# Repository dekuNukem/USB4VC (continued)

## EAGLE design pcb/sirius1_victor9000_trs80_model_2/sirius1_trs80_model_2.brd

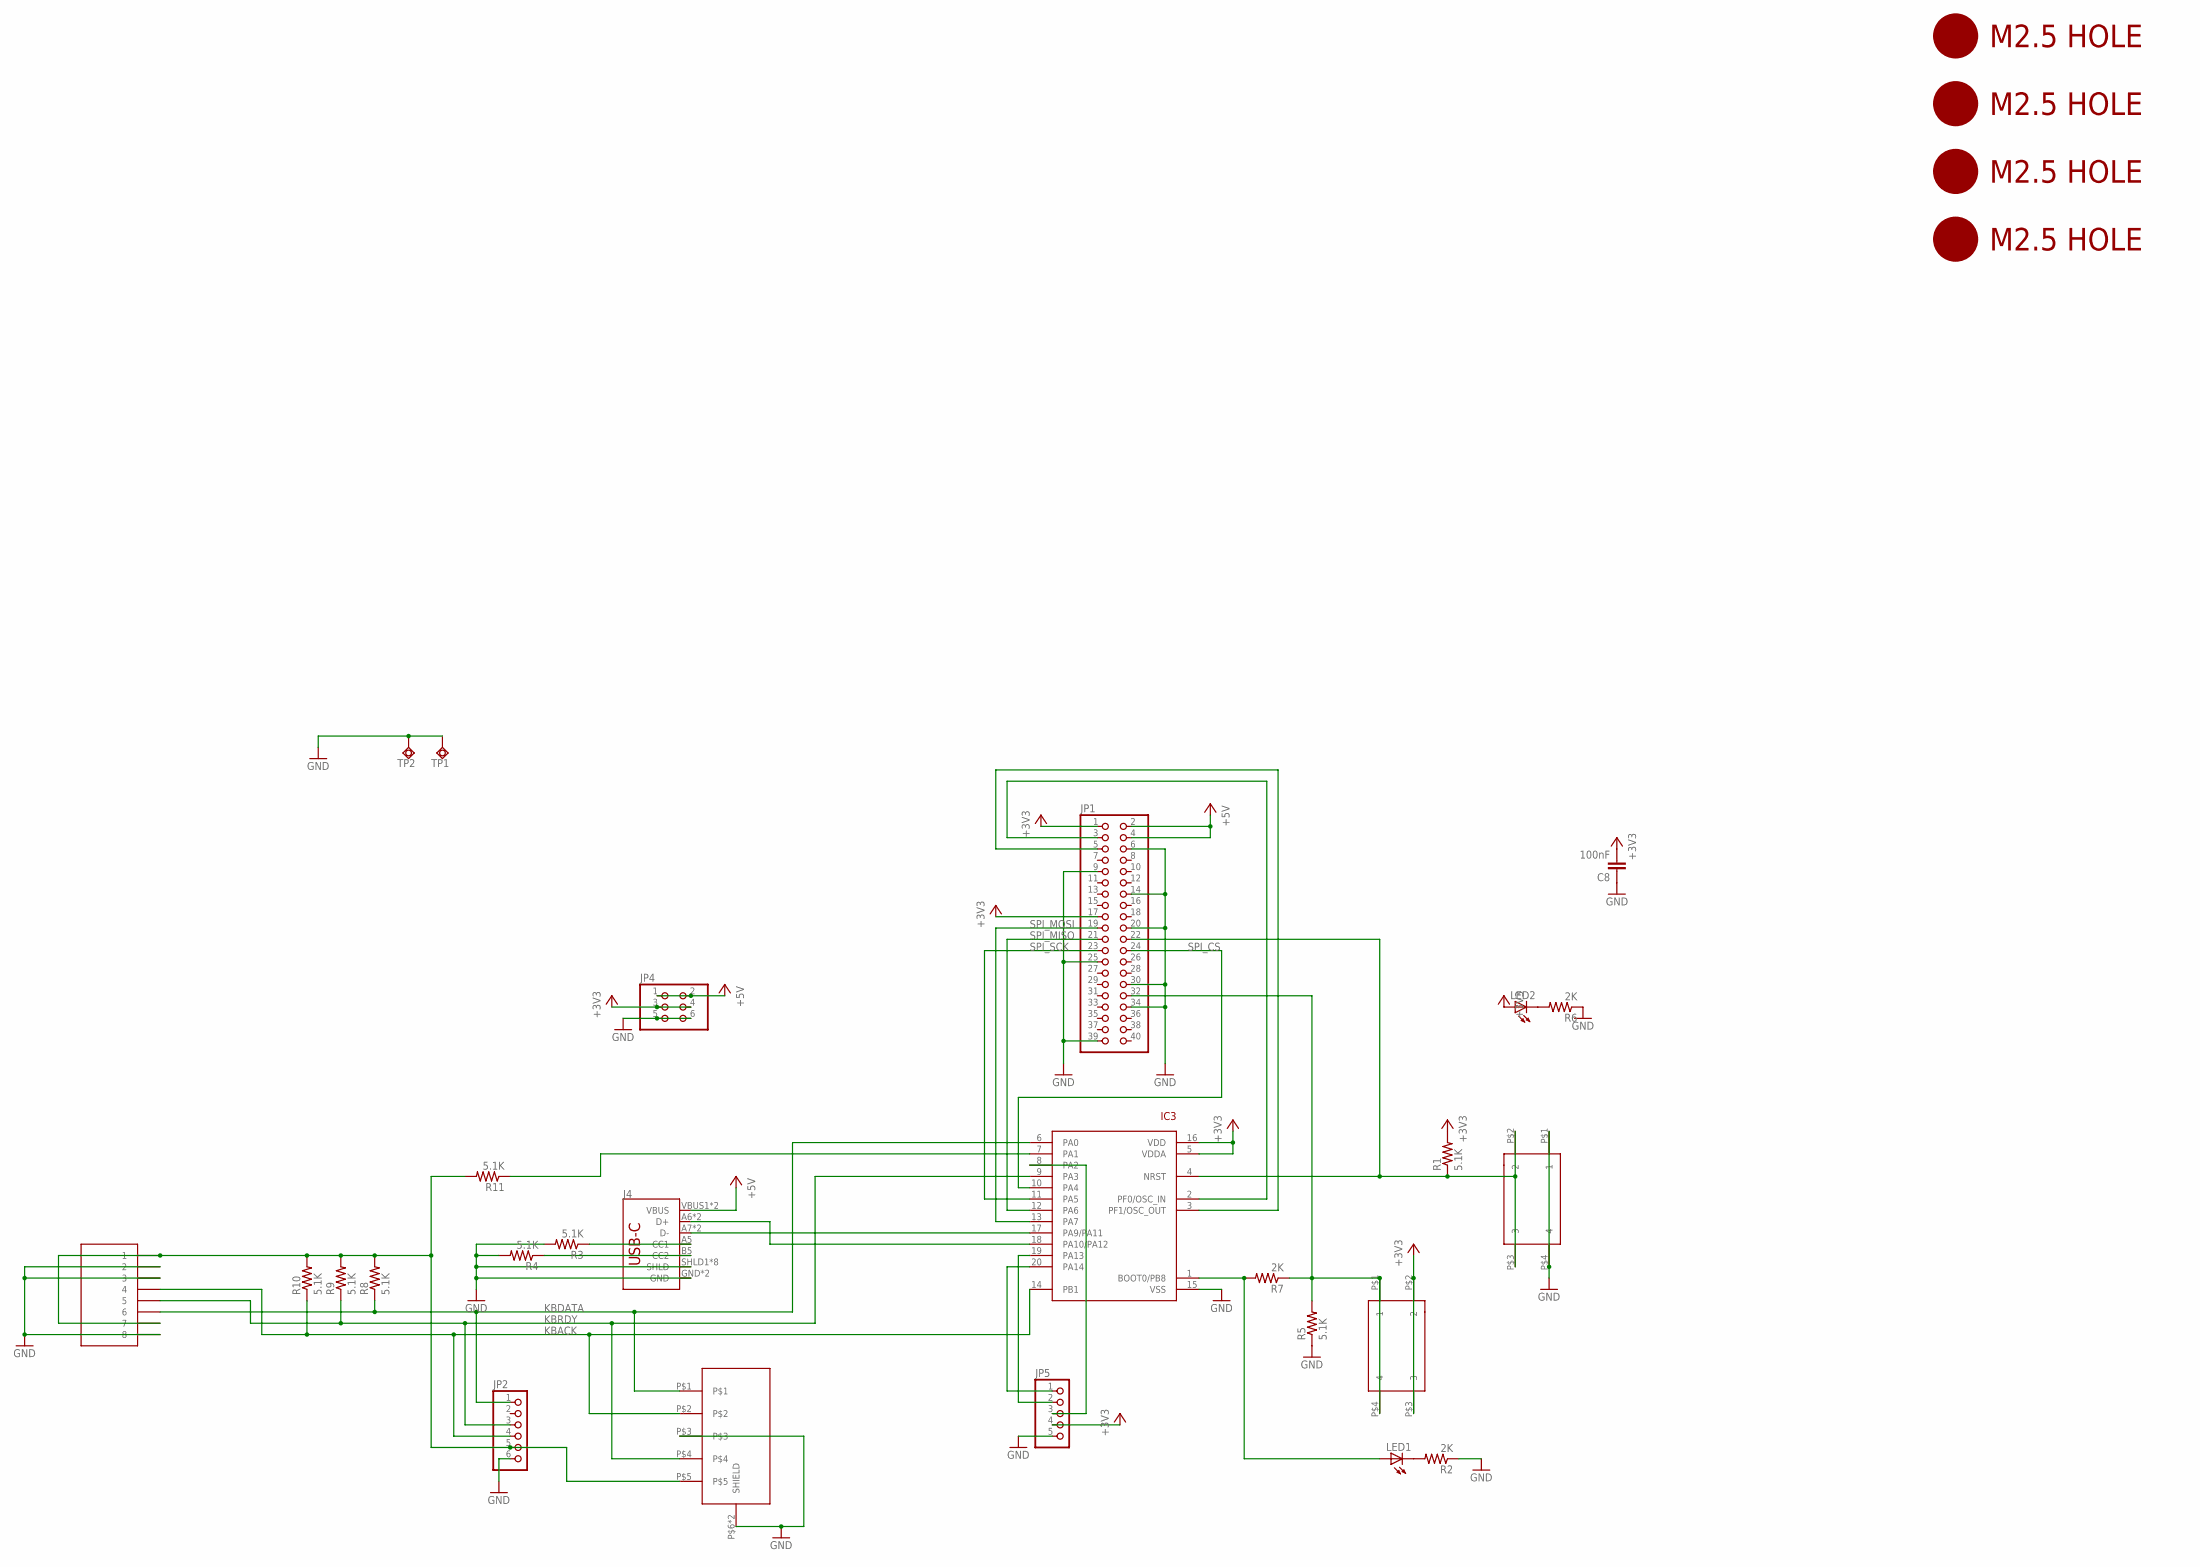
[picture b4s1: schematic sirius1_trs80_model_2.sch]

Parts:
C8: 100nF; 0805@1
IC3: STM32F042F4; TSSOP20
J4: USB_C16PIN; USB-C-16P
JP1: PINHD-2X20-BIG; 2X20-BIG
JP2: PINHD-1X6; 1X06
JP4: PINHD-2X3; 2X03
JP5: PINHD-1X5; 1X05
LED1, LED2: LEDCHIP-LED0805; CHIP-LED0805
R1, R3, R4, R5, R8, R9, R10, R11: 5.1K; 0805
R2, R6, R7: 2K; 0805
SW1, SW4: 324_SW; 342_SWICH_FOOT
TP1, TP2: TPSQPAD1-17; P1-17
U1: RJ45; RJ45-8
U$1: DIN5
U$2, U$3, U$4, U$5: M2.5HOLE

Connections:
+3V3: C8.2, IC3.5 (VDDA), IC3.16 (VDD), JP1.1, JP1.17, JP4.3, JP4.4, JP5.4, LED2.A, R1.2, SW1.P$2 (2), SW1.P$3 (3)
+5V: J4.VBUS1 (VBUS), J4.VBUS2 (VBUS), JP1.2, JP1.4, JP4.1, JP4.2
GND: C8.1, IC3.15 (VSS), J4.GND, J4.GND2 (GND), J4.SHLD1 (SHLD), J4.SHLD2 (SHLD), J4.SHLD3 (SHLD), J4.SHLD4 (SHLD), J4.SHLD5 (SHLD), J4.SHLD6 (SHLD), J4.SHLD7 (SHLD), J4.SHLD8 (SHLD), JP1.6, JP1.9, JP1.14, JP1.20, JP1.25, JP1.30, JP1.34, JP1.39, JP2.6, JP4.5, JP4.6, JP5.5, R2.1, R3.2, R4.2, R5.1, R6.1, SW4.P$1 (1), SW4.P$4 (4), TP1.TP, TP2.TP, U1.2, U1.3, U1.8, U$1.P$3, U$1.P$6 (SHIELD), U$1.P$7 (SHIELD)
KBACK: IC3.14 (PB1), JP2.4, R10.1, U1.4, U$1.P$2
KBDATA: IC3.6 (PA0), JP2.1, R8.1, U1.6, U$1.P$1
KBRDY: IC3.9 (PA3), JP2.3, R9.1, U1.5, U$1.P$4
unnamed: J4.A5 (CC1), R3.1
unnamed: JP1.32, R5.2, R7.1, SW1.P$1 (1), SW1.P$4 (4)
unnamed: IC3.17 (PA9/PA11), J4.A7 (D-), J4.B7 (D-)
unnamed: IC3.7 (PA1), R11.1
unnamed: IC3.8 (PA2), JP5.3
unnamed: IC3.19 (PA13), JP5.2
unnamed: J4.B5 (CC2), R4.1
unnamed: IC3.20 (PA14), JP5.1
unnamed: IC3.1 (BOOT0/PB8), LED1.A, R7.2
unnamed: IC3.2 (PF0/OSC_IN), JP1.3
unnamed: IC3.3 (PF1/OSC_OUT), JP1.5
unnamed: IC3.4 (NRST), JP1.22, R1.1, SW4.P$2 (2), SW4.P$3 (3)
unnamed: IC3.18 (PA10/PA12), J4.A6 (D+), J4.B6 (D+)
unnamed: LED1.C, R2.2
unnamed: JP2.5, R8.2, R9.2, R10.2, R11.2, U1.1, U1.7, U$1.P$5
unnamed: LED2.C, R6.2
SPI_CS: IC3.10 (PA4), JP1.24
SPI_MISO: IC3.12 (PA6), JP1.21
SPI_MOSI: IC3.13 (PA7), JP1.19
SPI_SCK: IC3.11 (PA5), JP1.23

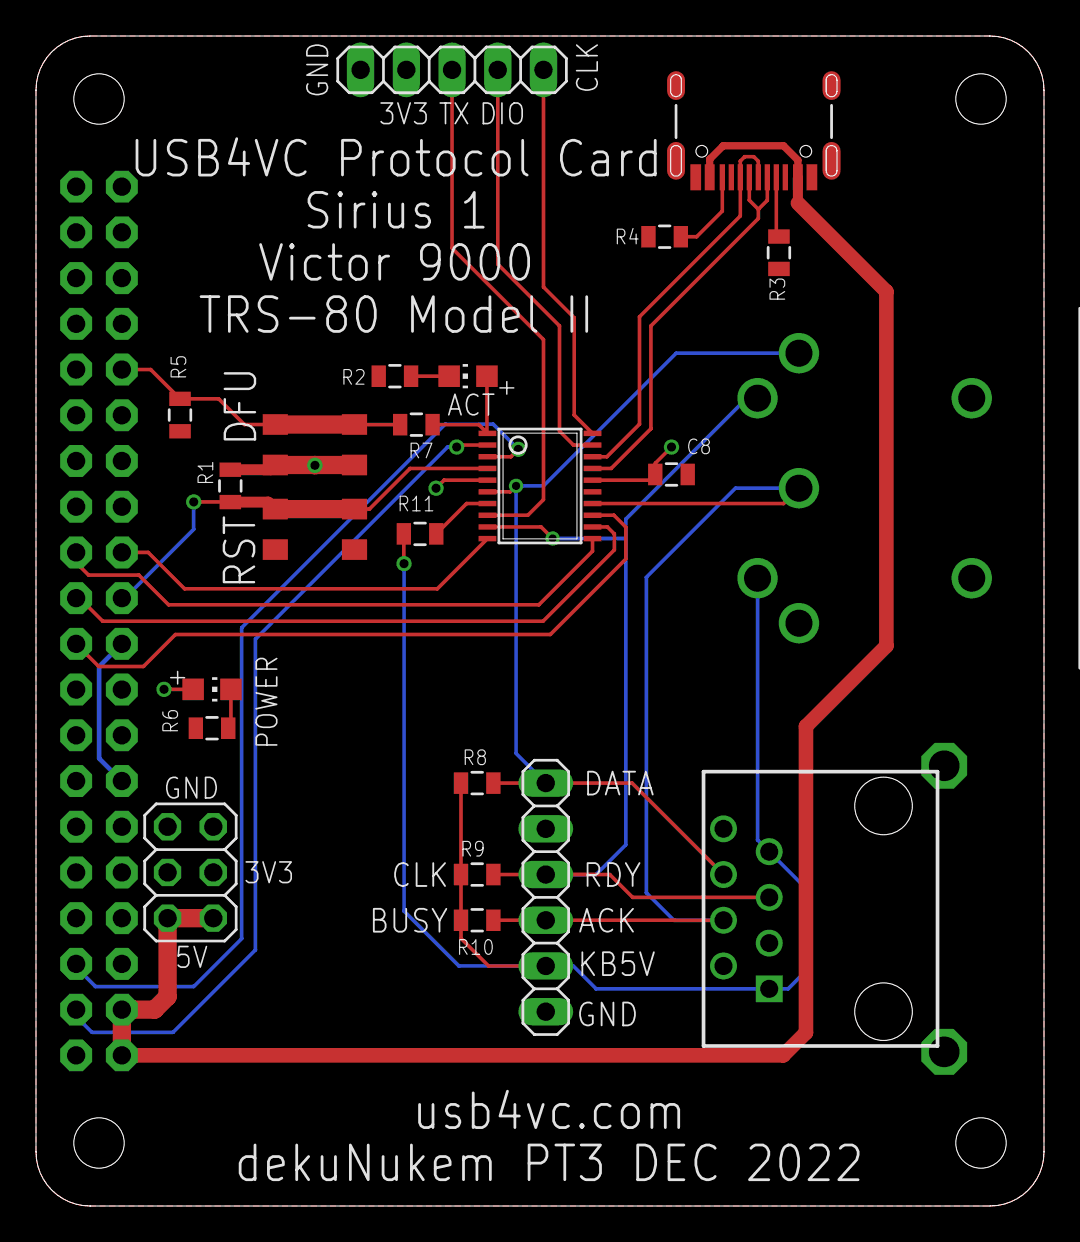
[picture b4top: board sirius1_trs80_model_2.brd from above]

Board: 2 copper layers, 56.0 x 65.0 mm, 30 parts (1 on the bottom side), 26 nets.

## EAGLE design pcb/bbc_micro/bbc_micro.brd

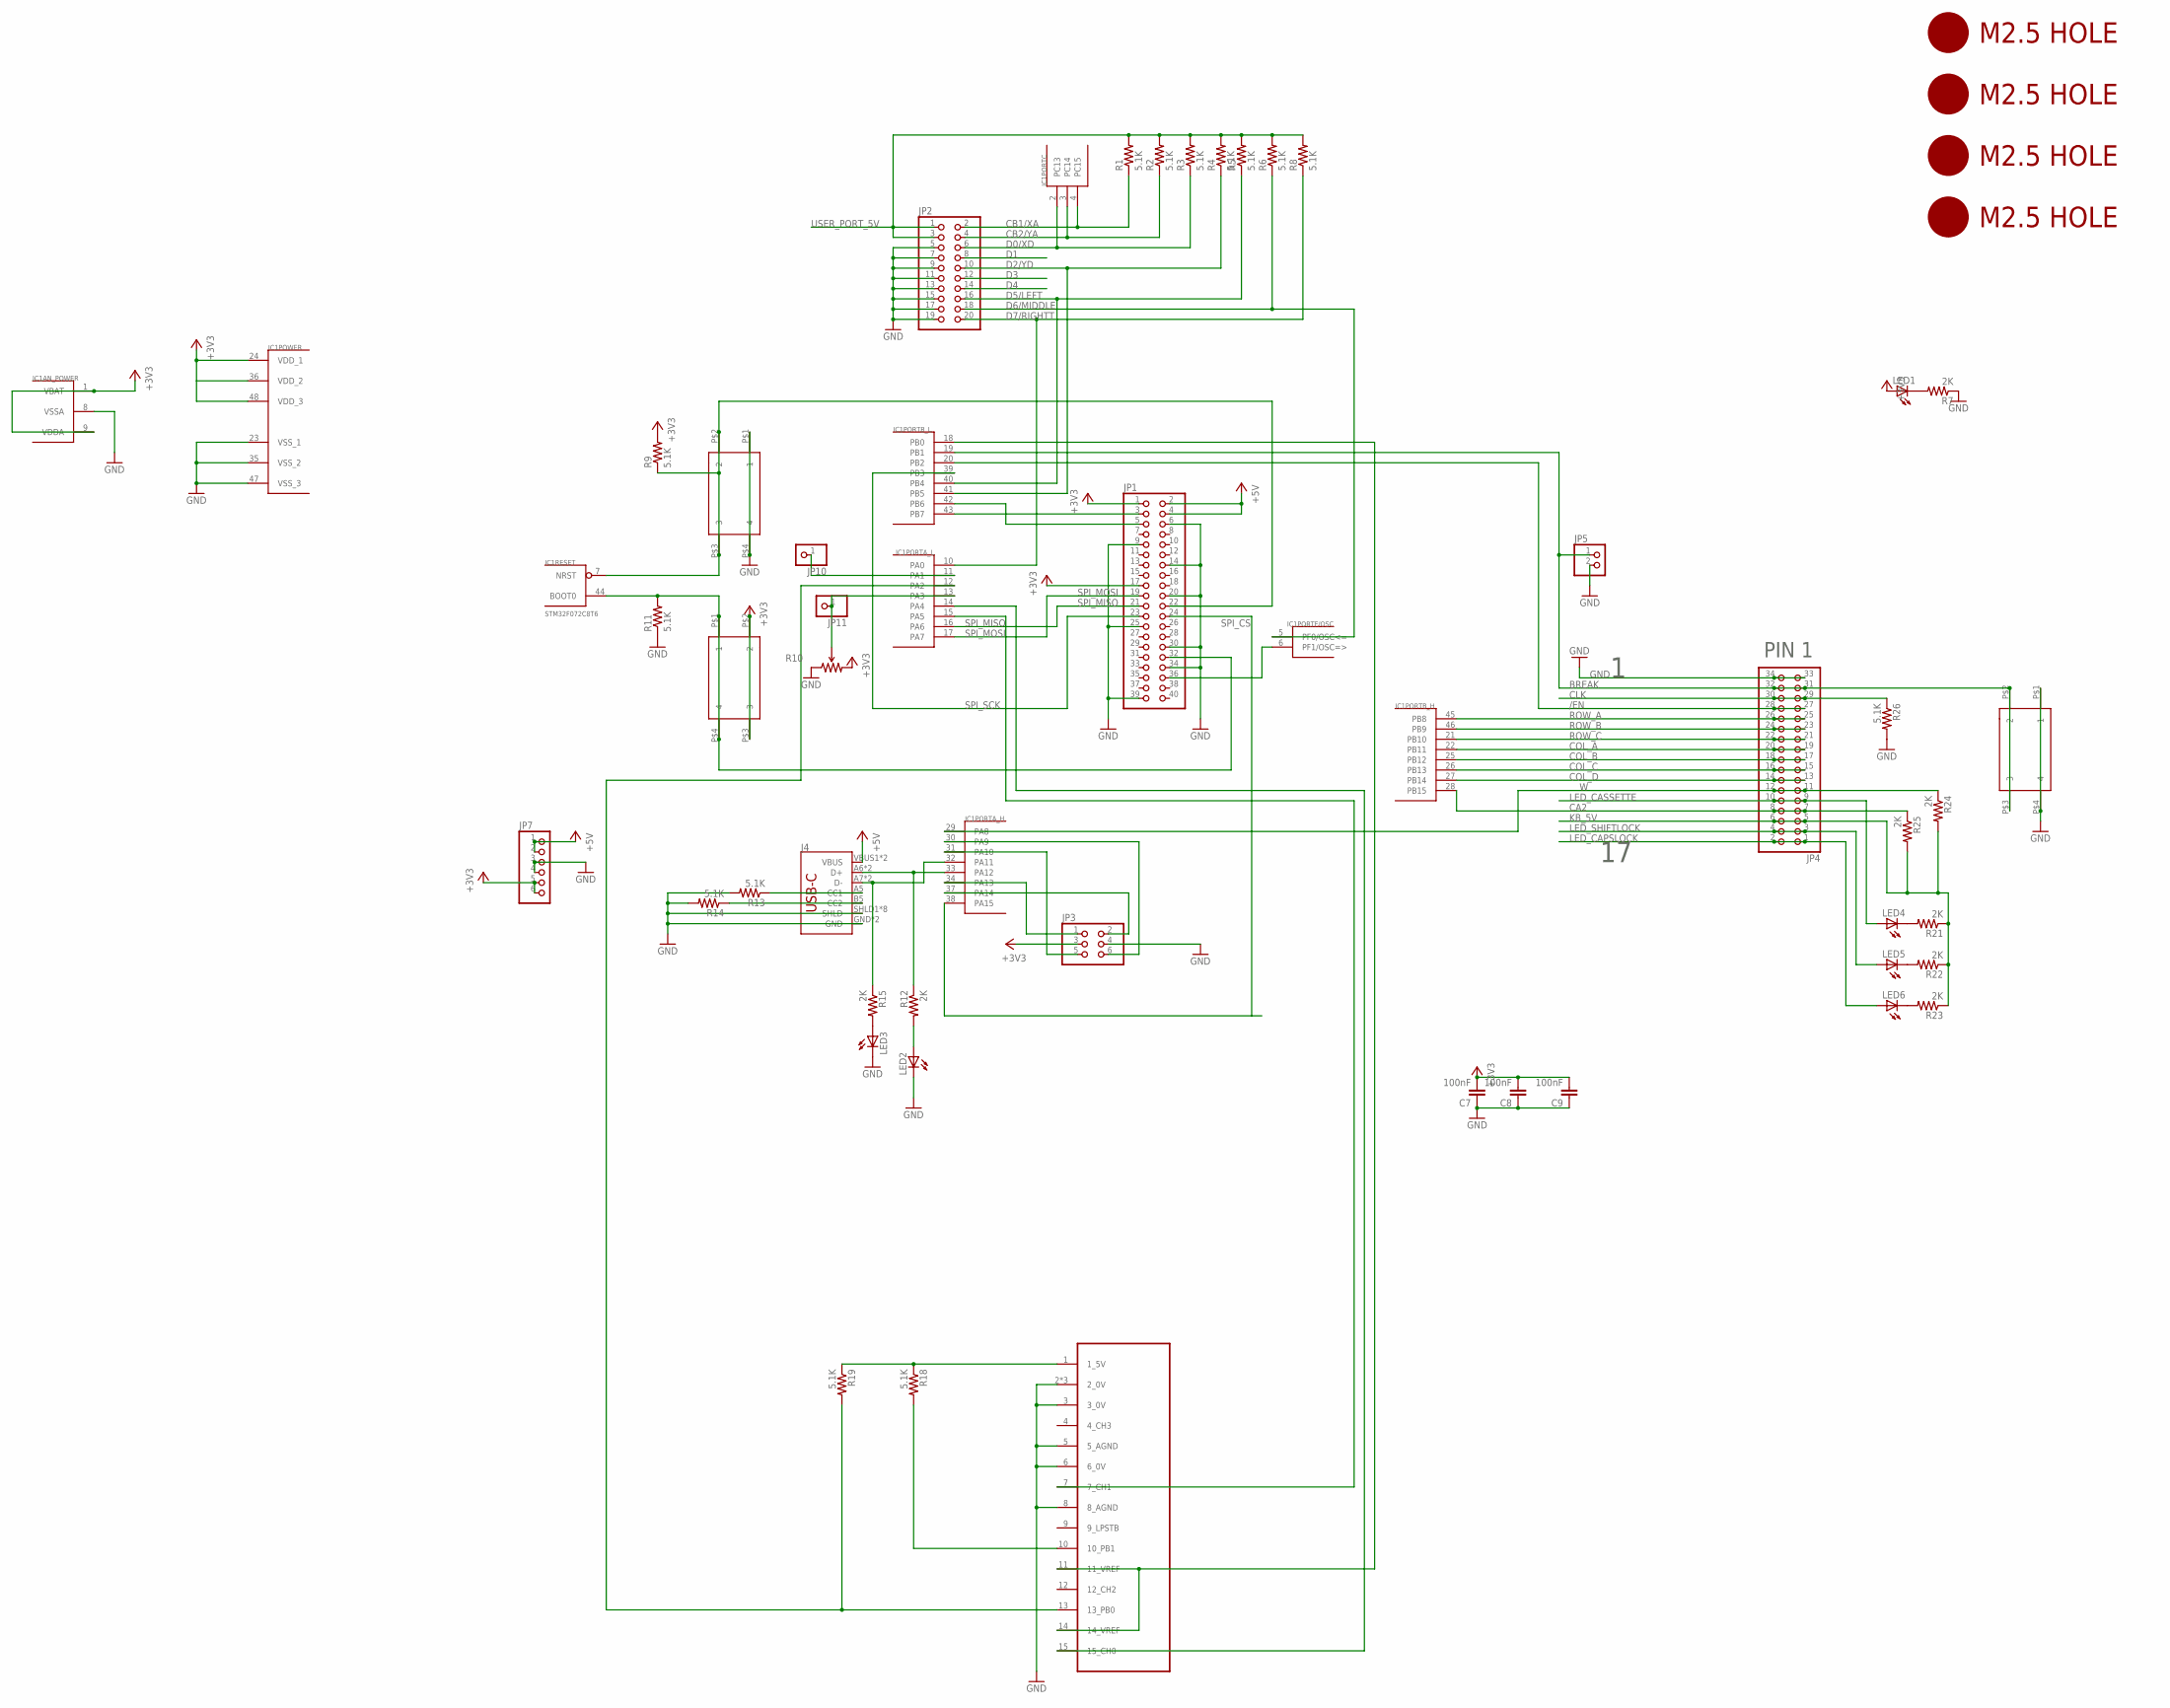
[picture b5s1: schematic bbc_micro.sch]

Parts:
C7, C8, C9: 100nF; 0805@1
IC1: STM32F072C8T6; TQFP48
J4: USB_C16PIN; USB-C-16P
JP1: PINHD-2X20-BIG; 2X20-BIG
JP2: PINHD-2X10/90; 2X10/90
JP3: PINHD-2X3; 2X03
JP4: PINHD-2X17/90; 2X17/90
JP5: PINHD-1X2; 1X02
JP7: PINHD-1X6CB; 1X06-CLEANBIG
JP10, JP11: PINHD-1X1CB; 1X01-CLEANBIG
LED1, LED2, LED3, LED4, LED5, LED6: LEDCHIP-LED0805; CHIP-LED0805
R1, R2, R3, R4, R5, R6, R8, R9, R11, R13, R14, R18, R19, R26: 5.1K; 0805
R7, R12, R15, R21, R22, R23, R24, R25: 2K; 0805
R10: TRIMPOTPTH; TRIM_POT_PTH
SW1, SW2, SW3: 324_SW; 342_SWICH_FOOT
U$2, U$3, U$6, U$7: M2.5HOLE
U$9: BBC_15P; DA15

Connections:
+3V3: C7.2, C8.2, C9.2, IC1.1 (VBAT), IC1.9 (VDDA), IC1.24 (VDD_1), IC1.36 (VDD_2), IC1.48 (VDD_3), JP1.1, JP1.17, JP3.3, JP7.5, JP7.6, LED1.A, R9.2, R10.3 (CW), SW2.P$2 (2), SW2.P$3 (3)
+5V: J4.VBUS1 (VBUS), J4.VBUS2 (VBUS), JP1.2, JP1.4, JP7.1, JP7.2
/EN: IC1.20 (PB2), JP4.27, JP4.28
BREAK: IC1.19 (PB1), JP4.31, JP4.32, JP5.1, SW3.P$2 (2), SW3.P$3 (3)
CA2: IC1.28 (PB15), JP4.7, JP4.8, R25.1
CB1/XA: IC1.4 (PC15), JP2.2, R1.1
CB2/YA: IC1.3 (PC14), JP2.4, R2.1
CLK: JP4.29, JP4.30, R26.1
COL_A: IC1.22 (PB11), JP4.19, JP4.20
COL_B: IC1.25 (PB12), JP4.17, JP4.18
COL_C: IC1.26 (PB13), JP4.15, JP4.16
COL_D: IC1.27 (PB14), JP4.13, JP4.14
D0/XD: IC1.2 (PC13), JP2.6, R3.1
D1: JP2.8
D2/YD: IC1.41 (PB5), JP2.10, R4.1
D3: JP2.12
D4: JP2.14
D5/LEFT: IC1.40 (PB4), JP2.16, R5.1
D6/MIDDLE: IC1.5 (PF0/OSC<=), JP2.18, R6.1
D7/RIGHTT: IC1.10 (PA0), JP2.20, R8.1
GND: C7.1, C8.1, C9.1, IC1.8 (VSSA), IC1.23 (VSS_1), IC1.35 (VSS_2), IC1.47 (VSS_3), J4.GND, J4.GND2 (GND), J4.SHLD1 (SHLD), J4.SHLD2 (SHLD), J4.SHLD3 (SHLD), J4.SHLD4 (SHLD), J4.SHLD5 (SHLD), J4.SHLD6 (SHLD), J4.SHLD7 (SHLD), J4.SHLD8 (SHLD), JP1.6, JP1.9, JP1.14, JP1.20, JP1.25, JP1.30, JP1.34, JP1.39, JP2.5, JP2.7, JP2.9, JP2.11, JP2.13, JP2.15, JP2.17, JP2.19, JP3.4, JP4.33, JP4.34, JP5.2, JP7.3, JP7.4, LED2.C, LED3.C, R7.1, R10.1 (CCW), R11.1, R13.2, R14.2, R26.2, SW1.P$1 (1), SW1.P$4 (4), SW3.P$1 (1), SW3.P$4 (4), U$9.2 (2_0V), U$9.3 (3_0V), U$9.5 (5_AGND), U$9.6 (6_0V), U$9.8 (8_AGND), U$9.G1 (2_0V), U$9.G2 (2_0V)
KB_5V: JP4.5, JP4.6, R21.1, R22.1, R23.1, R24.2, R25.2
LED_CAPSLOCK: JP4.1, JP4.2, LED6.A
LED_CASSETTE: JP4.9, JP4.10, LED4.A
LED_SHIFTLOCK: JP4.3, JP4.4, LED5.A
unnamed: J4.A5 (CC1), R13.1
unnamed: LED2.A, R12.2
unnamed: LED4.C, R21.2
unnamed: IC1.14 (PA4), U$9.15 (15_CH0)
unnamed: IC1.15 (PA5), U$9.7 (7_CH1)
unnamed: IC1.31 (PA10), JP3.5
unnamed: J4.B5 (CC2), R14.1
unnamed: IC1.33 (PA12), J4.A6 (D+), J4.B6 (D+), R12.1
unnamed: IC1.32 (PA11), J4.A7 (D-), J4.B7 (D-), R15.1
unnamed: IC1.18 (PB0), U$9.11 (11_VREF), U$9.14 (14_VREF)
unnamed: IC1.11 (PA1), JP10.1
unnamed: IC1.13 (PA3), JP11.1, R10.2 (WIPER)
unnamed: IC1.7 (NRST), JP1.22, R9.1, SW1.P$2 (2), SW1.P$3 (3)
unnamed: IC1.30 (PA9), JP3.6
unnamed: IC1.34 (PA13), JP3.1
unnamed: IC1.37 (PA14), JP3.2
unnamed: IC1.44 (BOOT0), JP1.32, R11.2, SW2.P$1 (1), SW2.P$4 (4)
unnamed: R18.1, R19.1, U$9.1 (1_5V)
unnamed: R18.2, U$9.10 (10_PB1)
unnamed: IC1.42 (PB6), JP1.5
unnamed: IC1.43 (PB7), JP1.3
unnamed: LED5.C, R22.2
unnamed: LED6.C, R23.2
unnamed: LED3.A, R15.2
unnamed: LED1.C, R7.2
unnamed: IC1.12 (PA2), R19.2, U$9.13 (13_PB0)
unnamed: IC1.6 (PF1/OSC=>), JP1.36
ROW_A: IC1.45 (PB8), JP4.25, JP4.26
ROW_B: IC1.46 (PB9), JP4.23, JP4.24
ROW_C: IC1.21 (PB10), JP4.21, JP4.22
SPI_CS: IC1.38 (PA15), JP1.24
SPI_MISO: IC1.16 (PA6), JP1.21
SPI_MOSI: IC1.17 (PA7), JP1.19
SPI_SCK: IC1.39 (PB3), JP1.23
USER_PORT_5V: JP2.1, JP2.3, R1.2, R2.2, R3.2, R4.2, R5.2, R6.2, R8.2
W: IC1.29 (PA8), JP4.11, JP4.12, R24.1

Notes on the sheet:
PIN 1

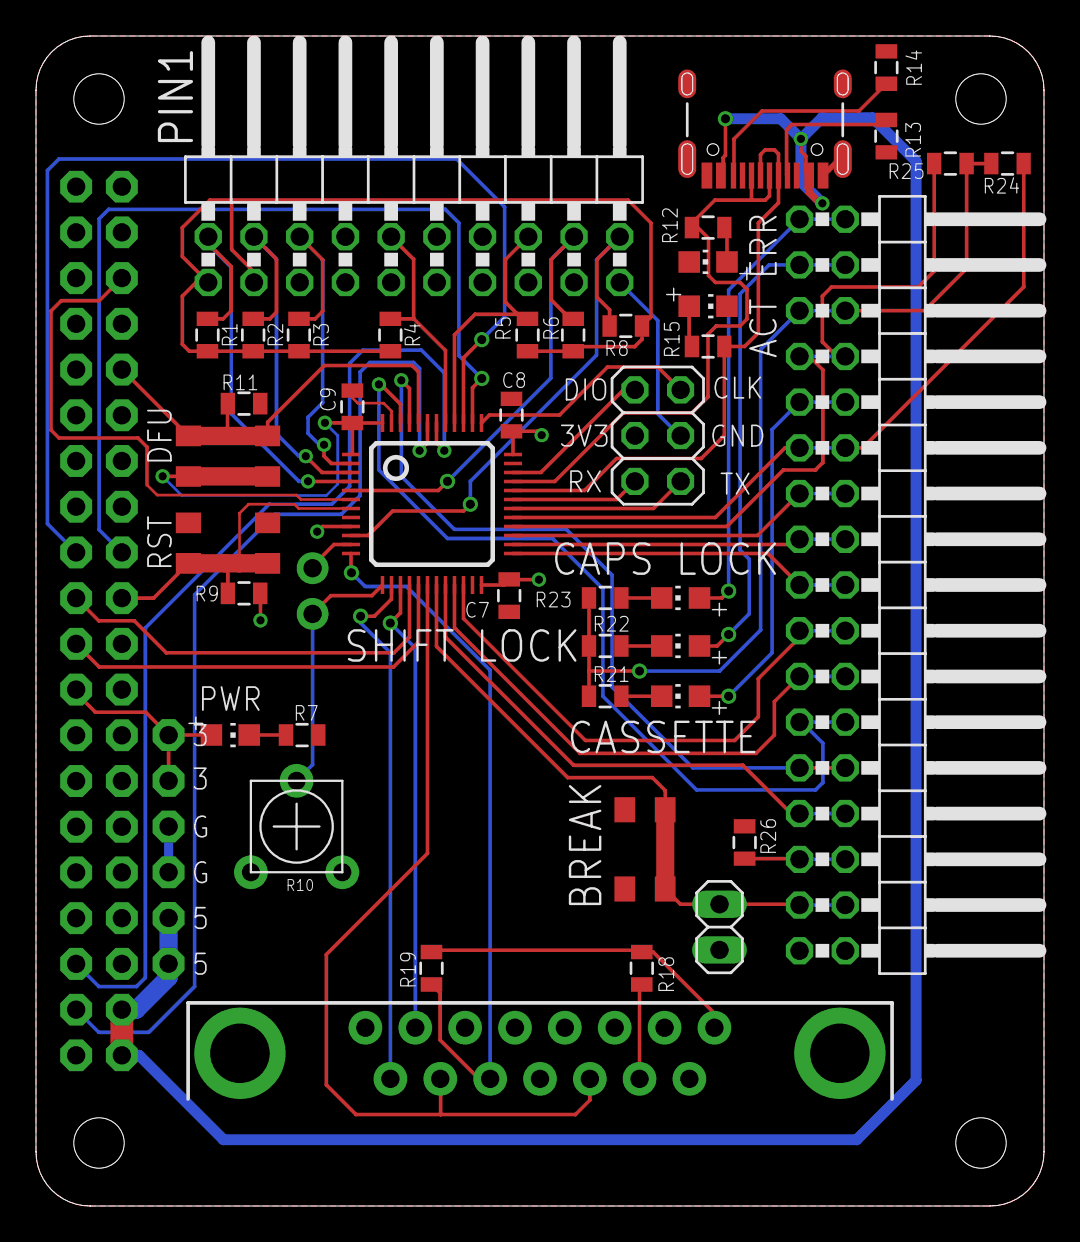
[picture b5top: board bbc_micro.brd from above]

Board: 2 copper layers, 56.0 x 65.0 mm, 50 parts (1 on the bottom side), 58 nets.

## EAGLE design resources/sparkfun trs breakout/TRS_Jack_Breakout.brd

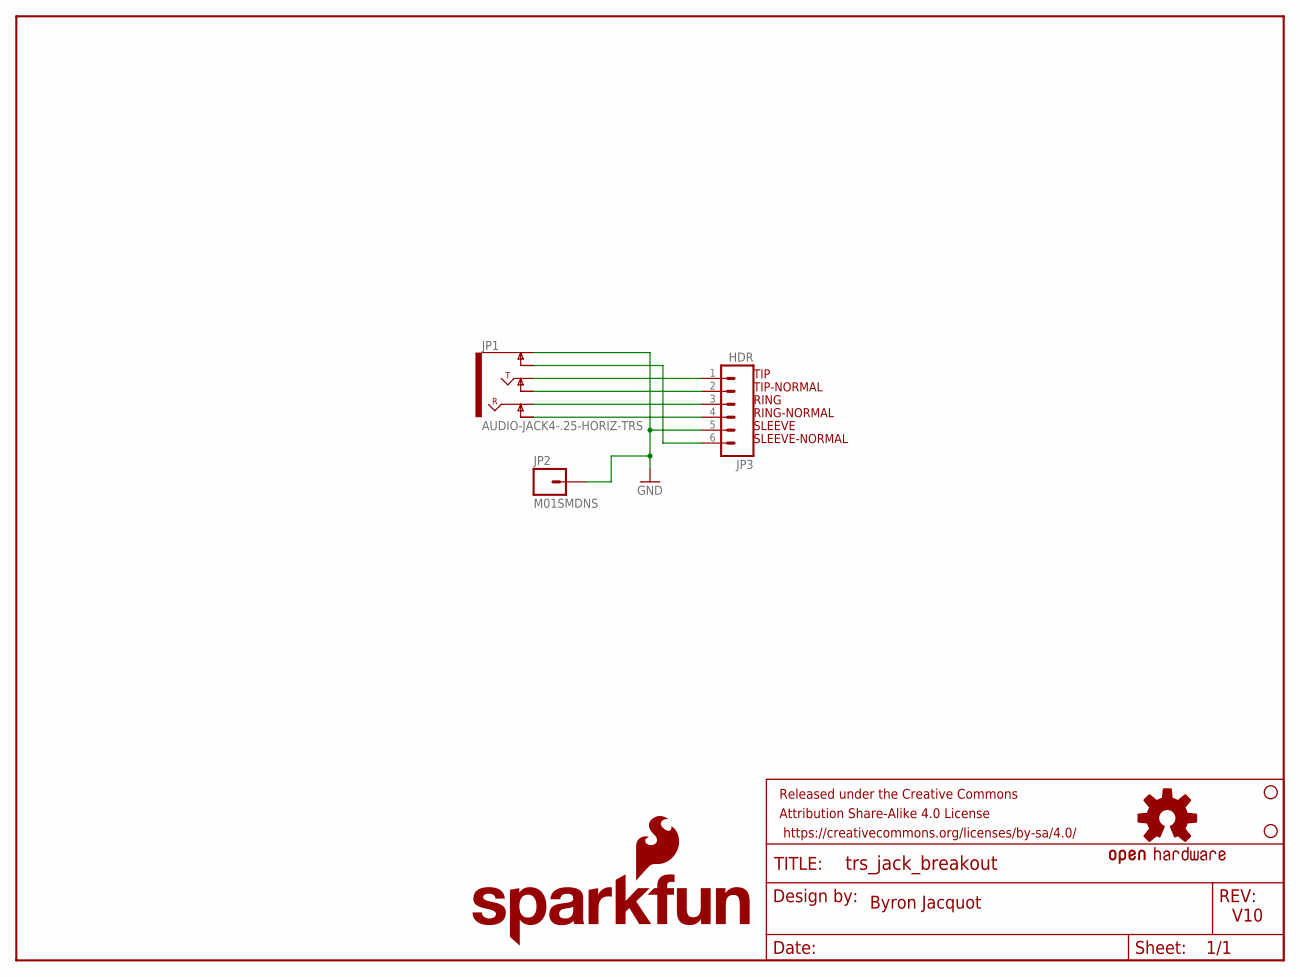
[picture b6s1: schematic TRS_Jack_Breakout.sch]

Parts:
FRAME1: FRAME-LETTER; CREATIVE_COMMONS
JP1: AUDIO-JACK4-.25-HORIZ-TRS; AUDIO-JACK-.25-INCH-HORIZ-PTH
JP2: M01SMDNS; 1X01NS
JP3: HDR; 1X06_NO_SILK
LOGO1: SFE_LOGO_NAME_FLAME.1_INCH; SFE_LOGO_NAME_FLAME_.1
LOGO2: OSHW-LOGOS; OSHW-LOGO-S
STANDOFF1, STANDOFF2: STAND-OFF

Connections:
GND: JP1.SLEEVE (EARTH), JP2.1, JP3.5
unnamed: JP1.TIP, JP3.1
unnamed: JP1.TIP-NORM, JP3.2
unnamed: JP1.RING, JP3.3
unnamed: JP1.RING-NORM, JP3.4
unnamed: JP1.SLEEVE-NORM (EARTH-NORM), JP3.6

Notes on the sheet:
Byron Jacquot
V10
TIP
TIP-NORMAL
RING
RING-NORMAL
SLEEVE
SLEEVE-NORMAL

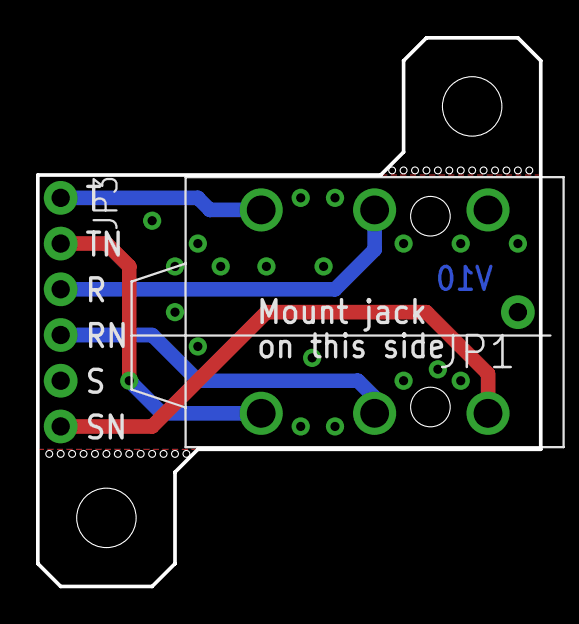
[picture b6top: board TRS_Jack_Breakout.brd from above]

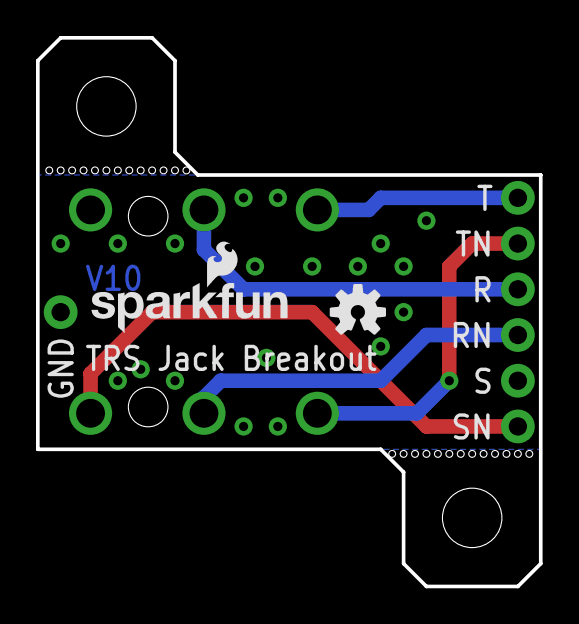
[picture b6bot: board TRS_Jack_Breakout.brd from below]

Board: 2 copper layers, 27.9 x 30.5 mm, 8 parts (2 on the bottom side), 6 nets.

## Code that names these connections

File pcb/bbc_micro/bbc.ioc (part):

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Mcu.Name=STM32F072C(8-B)Tx
Mcu.Package=LQFP48
Mcu.UserName=STM32F072C8Tx
PA0.GPIOParameters=GPIO_Label
PA0.GPIO_Label=MOUSE_RIGHT
PA0.Signal=GPIO_Output
PA1.GPIOParameters=GPIO_Label
PA1.GPIO_Label=JS2_BTN0
PA1.Signal=GPIO_Output
PA11.Mode=Device
PA11.Signal=USB_DM
PA12.Mode=Device
PA12.Signal=USB_DP
PA13.Mode=Serial_Wire
PA13.Signal=SYS_SWDIO
PA14.Mode=Serial_Wire
PA14.Signal=SYS_SWCLK
PA15.Mode=NSS_Signal_Hard_Input
PA15.Signal=SPI1_NSS
PA2.GPIOParameters=GPIO_Label
PA2.GPIO_Label=BUTTON0
PA2.Signal=GPIO_Output
PA3.GPIOParameters=GPIO_Label
PA3.GPIO_Label=BUTTON1
PA3.Signal=GPIO_Output
PA4.Signal=COMP_DAC1_group
PA5.Signal=COMP_DAC2_group
PA6.Mode=Full_Duplex_Slave
PA6.Signal=SPI1_MISO
PA7.Mode=Full_Duplex_Slave
PA7.Signal=SPI1_MOSI
PA8.GPIOParameters=GPIO_Label
PA8.GPIO_Label=W
PA8.Signal=GPIO_Output
PA9.Mode=Half_duplex(single_wire_mode)
PA9.Signal=USART1_TX
PB0.GPIOParameters=GPIO_Label
PB0.GPIO_Label=JS2_BTN1
PB0.Signal=GPIO_Output
PB1.GPIOParameters=GPIO_Label
PB1.GPIO_Label=KB_BREAK
PB1.Signal=GPIO_Input
PB10.GPIOParameters=GPIO_Label
PB10.GPIO_Label=KB_ROW_C
PB10.Signal=GPIO_Input
PB11.GPIOParameters=GPIO_Label
PB11.GPIO_Label=KB_COL_A
PB11.Signal=GPIO_Input
PB12.GPIOParameters=GPIO_Label
PB12.GPIO_Label=KB_COL_B
PB12.Signal=GPIO_Input
PB13.GPIOParameters=GPIO_Label
PB13.GPIO_Label=KB_COL_C
PB13.Signal=GPIO_Input
PB14.GPIOParameters=GPIO_Label
PB14.GPIO_Label=KB_COL_D
PB14.Signal=GPIO_Input
PB15.GPIOParameters=GPIO_Label
PB15.GPIO_Label=CA2
PB15.Signal=GPIO_Input
PB2.GPIOParameters=GPIO_Label
PB2.GPIO_Label=KB_EN
PB2.Signal=GPXTI2
PB3.Mode=Full_Duplex_Slave
PB3.Signal=SPI1_SCK
PB4.GPIOParameters=GPIO_Label
PB4.GPIO_Label=MOUSE_LEFT
PB4.Signal=GPIO_Output
PB5.GPIOParameters=GPIO_Label
PB5.GPIO_Label=MOUSE_YD
PB5.Signal=GPIO_Output
PB6.Mode=I2C
PB6.Signal=I2C1_SCL
PB7.Mode=I2C
PB7.Signal=I2C1_SDA
PB8.GPIOParameters=GPIO_Label
PB8.GPIO_Label=KB_ROW_A
PB8.Signal=GPIO_Input
PB9.GPIOParameters=GPIO_Label
PB9.GPIO_Label=KB_ROW_B
PB9.Signal=GPIO_Input
PC13.GPIOParameters=GPIO_Label
PC13.GPIO_Label=MOUSE_XD
PC13.Signal=GPIO_Output
PC14-OSC32_IN.GPIOParameters=GPIO_Label
PC14-OSC32_IN.GPIO_Label=MOUSE_YA
PC14-OSC32_IN.Signal=GPIO_Output
PC15-OSC32_OUT.GPIOParameters=GPIO_Label
PC15-OSC32_OUT.GPIO_Label=MOUSE_XA
PC15-OSC32_OUT.Signal=GPIO_Output
PF0-OSC_IN.GPIOParameters=GPIO_Label
PF0-OSC_IN.GPIO_Label=MOUSE_MID
PF0-OSC_IN.Signal=GPIO_Output
PF1-OSC_OUT.GPIOParameters=PinState,GPIO_Label
PF1-OSC_OUT.GPIO_Label=SLAVE_REQ
PF1-OSC_OUT.PinState=GPIO_PIN_RESET
PF1-OSC_OUT.Signal=GPIO_Output
RCC.SYSCLKFreq_VALUE=48000000
RCC.SYSCLKSource=RCC_SYSCLKSOURCE_HSI48
board=custom

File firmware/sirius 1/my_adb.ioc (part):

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Mcu.Name=STM32F042F6Px
Mcu.Package=TSSOP20
Mcu.UserName=STM32F042F6Px
PA0.GPIOParameters=PinState,GPIO_Label,GPIO_ModeDefaultOutputPP
PA0.GPIO_Label=KBDATA
PA0.GPIO_ModeDefaultOutputPP=GPIO_MODE_OUTPUT_OD
PA0.PinState=GPIO_PIN_SET
PA0.Signal=GPIO_Output
PA1.GPIOParameters=GPIO_PuPd,GPIO_Label
PA1.GPIO_Label=KB5V
PA1.GPIO_PuPd=GPIO_PULLDOWN
PA1.Signal=GPIO_Input
PA13.Mode=Serial_Wire
PA13.Signal=SYS_SWDIO
PA14.Mode=Serial_Wire
PA14.Signal=SYS_SWCLK
PA2.Mode=Half_duplex(single_wire_mode)
PA2.Signal=USART2_TX
PA3.GPIOParameters=PinState,GPIO_Label,GPIO_ModeDefaultOutputPP
PA3.GPIO_Label=KBRDY
PA3.GPIO_ModeDefaultOutputPP=GPIO_MODE_OUTPUT_OD
PA3.PinState=GPIO_PIN_SET
PA3.Signal=GPIO_Output
PA4.Mode=NSS_Signal_Hard_Input
PA4.Signal=SPI1_NSS
PA5.Mode=Full_Duplex_Slave
PA5.Signal=SPI1_SCK
PA6.Mode=Full_Duplex_Slave
PA6.Signal=SPI1_MISO
PA7.Mode=Full_Duplex_Slave
PA7.Signal=SPI1_MOSI
PB1.GPIOParameters=GPIO_Label
PB1.GPIO_Label=KBACK
PB1.Signal=GPIO_Input
PB8.GPIOParameters=GPIO_Label
PB8.GPIO_Label=USER_LED
PB8.Signal=GPIO_Output
RCC.SYSCLKFreq_VALUE=48000000
RCC.SYSCLKSource=RCC_SYSCLKSOURCE_HSI48
board=custom

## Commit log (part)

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2022-02-05 fixed firmware update bug, fixed ertm disable bug, handle input scan exceptions, added xbox controller driver note
2022-02-05 updated disiabling ertm instructions
2022-02-05 updated ertm scan frequency
2022-02-05 updated protocol display name, added exception handling in custom gamepad mapping
2022-02-05 added kickstarter info
2022-02-05 added pcards photo
2022-02-06 added rpi photo
2022-02-06 added more exception handling
2022-02-06 added table of contents
2022-02-06 new header gif
2022-02-07 fixed youtube video link
2022-02-08 updated project goals
2022-02-12 minor code fix, rearranged README sections, updated launch info
2022-02-13 fixed bugs
2022-02-13 fixed analog trigger detection
2022-02-13 now detecting gamepad type nativelly
2022-02-14 adjusted default ibm ggp mapping to suit xpadneo
2022-02-14 fixed typo, added more analog trigger check
2022-02-14 changed wording
2022-02-14 removed cursor
2022-02-14 added known issues
2022-02-14 fixed joycheck link
2022-02-14 updated docs
2022-02-14 added warnings about cable
2022-02-14 fixed typos
2022-02-15 added model change detection, recompiles bluetooth if so
2022-02-17 updated wording
2022-02-17 updated known issues
2022-02-17 added OG mac keyboard breakout
2022-02-17 started working on OG macintosh protocol
2022-02-17 started quad encoder test
2022-02-17 quad increment and decrement working
2022-02-22 updated documents
2022-02-22 updated kickstarter links
2022-02-23 updated pcb silkscreens for first production run
2022-02-25 fixed playstation 5 dualsense controller default mapping
2022-02-25 added ps5 custom map codes
2022-02-25 updated ps5 and xbox controller default mapping, added default mouse and keyboard mapping
2022-02-25 detecting gamepad type using usb vendor and product id, added support for PS4 controller, added deadzone filtering to reduce unneeded SPI message
2022-03-01 updated rpi app version number
2022-03-03 minor adjustments
2022-03-07 working on showing ev codes on OLED
2022-03-08 added exiting event code display, updated version number
2022-03-08 changed ev code viewer text
2022-03-08 updated exception message
2022-03-11 added baseboard pinout
2022-03-11 reduced main page update frequency
2022-03-12 reduced duplicate mouse packets
2022-03-12 updating technical documents
2022-03-12 updated p-card interrupt information and other technical docs
2022-03-12 working on make-your-own protocol card doc
2022-03-13 minor wording change
2022-03-13 fix typo
2022-03-16 updated post-kickstarter information
2022-03-18 fixed switch pro controller button not holding down, added compatibility matrix, updated doc
2022-03-19 updated doc about gamepad
2022-03-19 updated compatibility matrix photo
2022-03-25 adjusted custom controller mapping name, updated default mapping
2022-03-25 added setting wifi info from config file
2022-03-25 fixed wifi info update
2022-03-26 before trying to adjust ARR on the fly
2022-03-26 ARR-based quad encoder output proof of concept working
2022-03-28 added mac plus keyboard capture, updated quad test code
2022-03-28 changed m0110 name
2022-03-28 updated scraps
2022-03-29 wrote firmware flasher
2022-03-29 added baseboard tester
2022-03-31 added ps5 mapping for supported gamepad raw output
2022-03-31 added ps4 controller
2022-03-31 added supported gamepads raw output
2022-04-01 fixed a typo
2022-04-02 updated RPi OS setup note
2022-04-02 updated clean OS setup notes, removed redundant wifi parsing
2022-04-02 added new source code packing script, added internet update code
2022-04-02 added firmware list get
2022-04-03 working on firmware download
2022-04-03 finished internet update and usb config loading
2022-04-03 fixed minor bugs on internet updates
2022-04-03 finishing touches
2022-04-05 updated baseboard tester script
2022-04-06 added wifi setup guide
2022-04-06 cleaned up doc
2022-04-06 working on IBMPC P-card testing firmware
2022-04-07 updated IBM PC P-card firmware to 0.2.0
2022-04-09 changed wifi config template to zip for easy download
2022-04-09 added tinkering guide and updated PCB information
2022-04-10 updated flasher script to support USB DFU
2022-04-10 added notes about event code viewer
2022-04-10 added instructions about labels
2022-04-25 forgot what i did
2022-04-25 added backer acknowledgements
2022-04-26 improved unsupported gamepad detection
2022-04-27 added support for more gamepad buttons
2022-04-27 removed debug printout
2022-04-27 0.1.1 rpi code release
2022-04-29 started working on new protocol card firmware
2022-04-29 working on mouse encoder
2022-04-30 quad encoder output working, not very linear though
2022-04-30 refractoring quad encoder code
2022-04-30 moved quad encoder into its own file
2022-04-30 updating quad struct
2022-04-30 quad mouse working, linearity needs tweaking
2022-05-01 added inhibit handling in xt keyboard
2022-05-02 fixing ps2 mouse inhibit bug
2022-05-02 ps2 mouse inhibit bug seems to be fixed, still more to do
2022-05-02 tested on computer itself, might need to add a seperate mode
2022-05-02 removed remote and wrap modes, added duel scroll wheel 5 button intellimouse support
2022-05-02 working on adding KVM compatibility mode
2022-05-03 added default mapping for unsupported gamepads
2022-05-03 added more buttons to raw unsupported gamepad packet
2022-05-03 cleaned up code
2022-05-04 setting up scan code set 3
2022-05-05 added linux ev code to set 3 lookup
2022-05-05 updated wifi and update instructions
2022-05-05 added new firmware
2022-05-06 Update kit_assembly.md
    Change 2.5mm standoffs to 2.5mm spacers
2022-05-06 added set 3 lookup tables
2022-05-06 added scancode set 3 change all key status commands
2022-05-06 final test for set 3
2022-05-06 removed separate kvm compatibility mode
2022-05-06 getting ready for update release
2022-05-06 added mousesystems serial mouse capture
2022-05-08 mouse systems serial mouse prototype working
2022-05-10 added mousesystems serial mouse support
2022-05-10 fixed more ps5 controller mapping
2022-05-10 removed debug print, updated IBMPC firmware
2022-05-10 added mousesystems serial mouse datasheet and new firmware
2022-05-13 added improved idle detection to ps/2 mouse too
2022-05-13 added ps/2 rate limiter
2022-05-13 preparing to add event consolidation
2022-05-13 rpi app will now add mousepoll parameter to cmdline.txt if doesnt exist
2022-05-13 updated product description
2022-05-18 added gamepad digitial protocol info
2022-05-19 working on overhauling ADB buffer
2022-05-19 reduced ADB card ISR latency, added mouse event consolidation
2022-05-19 added watchdog timer on ADB card
2022-05-20 added sending ADB message when pressing power button on the PCB
2022-05-20 added new ADB firmware
2022-05-20 adjusted ADB card debug pin setup
2022-05-20 uploaded new IBM PC firmware
2022-05-21 Fix spamming debug log for PIs w/o bluetooth
2022-06-23 new firmware, fixed XT keyboard mapping and better serial mouse RTS handlign
2022-06-24 resumed working on m0110a
2022-06-24 m0110a read seems to be working
2022-06-24 m0110a write working but needs to add 250ms timeout
2022-06-24 moving m1100 into own function
2022-06-26 added capture for m0110a keypad keys
2022-06-26 m0100a outbuf write seems to work, need more error handling
2022-06-27 single byte mapping working
2022-06-30 apple_all p-card prototype #2
2022-07-04 added mac mouse power detect
2022-07-07 adjusted prototype pcb
2022-07-22 testing firmware on new board
2022-08-02 new curve for quad mouse
2022-08-02 added mouse event consolidation to m0100 mouse, fixed buttons, tested working
2022-08-03 added enabling and disabling M0100 mouse, tested
2022-08-04 working on bbc micro
2022-08-05 working on bbc micro PCB
2022-08-05 hooked up digital pot and leds
2022-08-06 bbc micro protocol board test board
2022-08-10 updated bbc pcard
2022-08-16 working on BBC pcard
2022-08-17 not quite working
2022-08-17 still not working
2022-08-18 reduced gpio write time
2022-08-18 barebone row col lookup working, timing still slightly off
2022-08-18 overclocked to 64MHz seems to be working
2022-08-18 before adding repeating CA2 interrupt
2022-08-18 keyboard matrix mostly complete but has multiple key scan bug
2022-08-18 before fixing missing input bug
2022-08-18 trying dumb delay
2022-09-04 wired up pullups
2022-09-04 added early support for BBC micro protocol card, not compelte
2022-09-05 changed to using built-in DAC
2022-09-12 improved debug pin speed, removed i2c digital pot
2022-09-12 trying to figure out how to track press duration
2022-09-12 trying to debug
2022-09-13 think i found the issue
2022-09-13 missing input seem fixed
2022-09-13 adding key remapping
2022-09-13 added reset, still need some work
2022-09-14 reset key working
2022-09-14 added compatibility with UK ISO PC keyboards
2022-09-14 fixed unmapped keys parsing
2022-09-16 keyboard behaving weird
2022-09-16 adc working
2022-09-16 now reading from ADC for BBC reference
2022-09-17 removed second joystick and added BBC VREF input
2022-09-18 before adding protocol select
2022-09-18 fixed a few minor bugs
2022-11-02 adjusted mapping
2022-11-02 added sirius 1 keyboard capture
2022-11-03 added sirius 1 pcard prototype
2022-11-10 kb write working
2022-11-10 keymap working
2022-11-10 updated keymaps
2022-11-10 added presence detection
2022-11-10 clean up wording
2022-11-29 added TRS-80 Model II keyboard capture
2022-11-29 more TRS-80 Model II keyboard capture
2022-11-29 more TRS-80 Model II video signal capture
2022-11-29 clean up doc
2022-12-01 started working on TRS-80 Model II
2022-12-13 test write working on real TRS80 M2
2022-12-14 added TRS-80 Model II keyboard connector
2022-12-18 updated apple_all protocol card
2023-01-01 adjusted footprint
2023-02-28 working on lisa kb
2023-02-28 lisa byte write working
2023-02-28 lisa init working on real hw
2023-03-01 adjusted timing, working on real lisa
2023-03-01 more testing on lisa
2023-03-03 prepare to add BUSY signal
2023-03-03 added busy pin and adjusted resistors
2023-03-03 added pcard busy signal
2023-03-03 updated photos
2023-03-03 quad mouse workinh
2023-03-04 m0110 keyboard working, added busy signal and protocol switching
2023-03-04 updated LED blink duration
2023-03-04 added ADB to new card
2023-03-04 fixed typo
2023-03-04 updated values
2023-03-04 added BUSY to ibm card
2023-03-04 added resistor to digipot
2023-03-06 updated IBM PC card
2023-03-07 BUSY signal now lasts the entire duration of ADB message
2023-03-07 added technical bulletin
2023-03-07 moved resistors
2023-03-07 changed names
2023-03-07 added timeout to BUSY wait
2023-03-07 added zip source script
2023-03-07 porting ADB busy to lisa card
2023-03-07 BUSY signal now lasts the whole ADB message
2023-03-07 adding BUSY signal to IBM card
2023-04-07 switched BUSY pin to PC14, tested working
2023-04-12 added more info about new card
2023-04-16 cleanup
2023-04-16 changed to correct firmware
2023-04-16 added new card fw update support
2023-04-19 added dfu firmware
2023-04-29 added review video
2023-04-30 added 200Hz rate limit for PS/2
2023-04-30 minor update for new IBM card production run
2023-05-01 fixed a minor baud rate bug
2023-07-02 forcing write before BAT
2023-07-02 that was wrong
2023-08-30 Add support for extended codes in PS/2 Keyboard set 1
2023-11-08 Update user_program to support running in an alternate install directory, plus handle 64bit kernel event data.
2024-02-27 Implement keyboard-triggered shutdown
    (Avoids the need to touch the USB4VC under normal operation in most
    cases, mitigating the lack of a case to protect from ESD.)
2024-03-14 working on porting to raspberry pi
2024-03-14 updated path, clean up code
2024-03-14 testing controllers
2024-10-28 using github pages
2025-08-16 new baseboard revision with more sturdy buttons
2025-08-18 updated setup instructions, dont compile xpadneo on RPi5
2025-08-22 adjusted USB polling rate
2025-08-23 evdev test
2025-08-23 Clarify unzipping method for boot image
2025-08-23 trying out async device scan
2025-08-24 moved over to asyncio
2025-08-24 minor bug
2025-08-24 restored old code
2025-08-24 removed joystick curve code
2025-08-24 new branch
2025-08-24 code cleanupo
2025-08-24 added arrows
2025-08-24 separate spi module, init works
2025-08-24 spi ask protocol works
2025-08-24 code cleanup
2025-08-24 working on input parsing, writing notes
2025-08-24 removed unused file, changing gamepad check
